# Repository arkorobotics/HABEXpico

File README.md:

# HABEXpico
Small High Altitude Balloon Payload

# Build & Flash Firmware
See /Firmware/README.md

# Run Test Suite
See /Testscripts/README.md

# TODO

- [DONE] Create NMEA and Nanoformat test scripts
- [DONE] Write NMEA parser library
- [DONE] Write Nanoformatter library
- [DONE] Test NMEA and Nanoformatter libraries using test script
- Write Radio lib
- Test Radio lib using test script
- Write Power Management lib
- Test Power Management lib using test scripts
- Write C&DH + state machine
- Test C&DH + state machine
- Bonus: Add VOR rx/triangulation with GPS ground truth and/or fallback (going to need a lot more memory)

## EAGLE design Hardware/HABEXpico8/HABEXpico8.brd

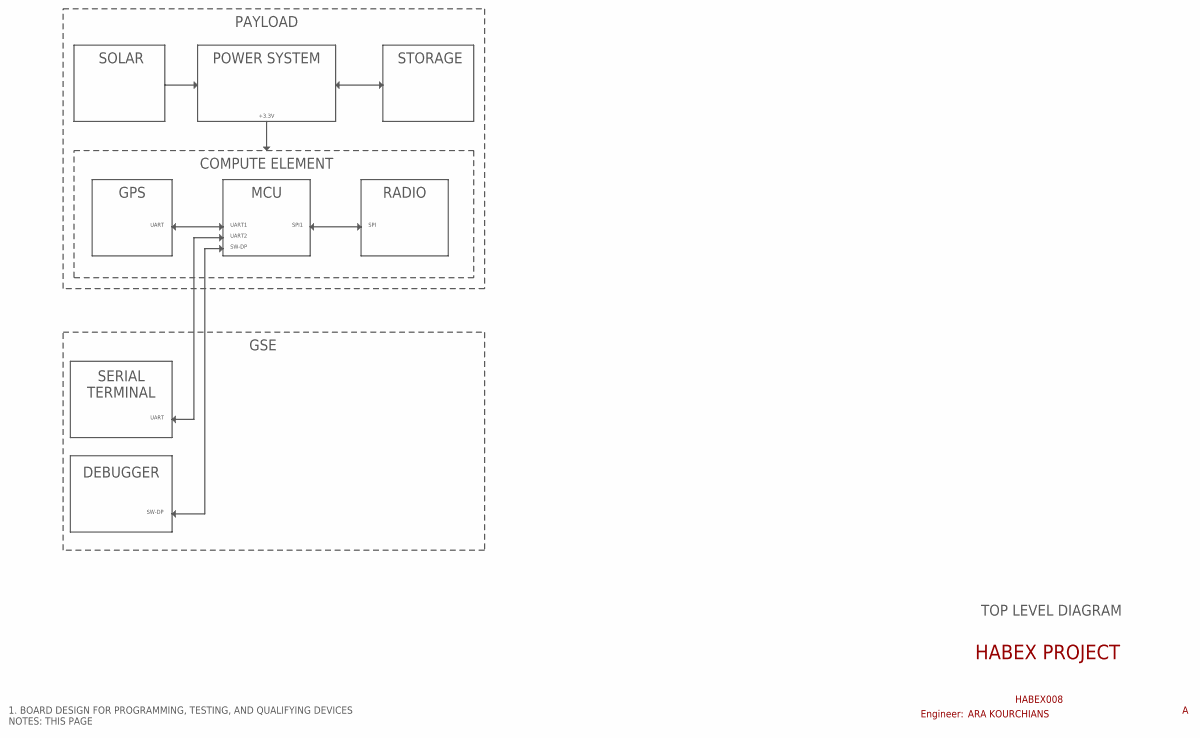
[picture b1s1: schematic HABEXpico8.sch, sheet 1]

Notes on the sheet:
1. BOARD DESIGN FOR PROGRAMMING, TESTING, AND QUALIFYING DEVICES NOTES: THIS PAGE
HABEX PROJECT
HABEX008
RADIO
MCU
GPS
UART
UART1
SPI1
SPI
ARA KOURCHIANS
Engineer:
TOP LEVEL DIAGRAM
SERIAL TERMINAL
COMPUTE ELEMENT
POWER SYSTEM
+3.3V
SOLAR
STORAGE
UART2
PAYLOAD
DEBUGGER
SW-DP
GSE

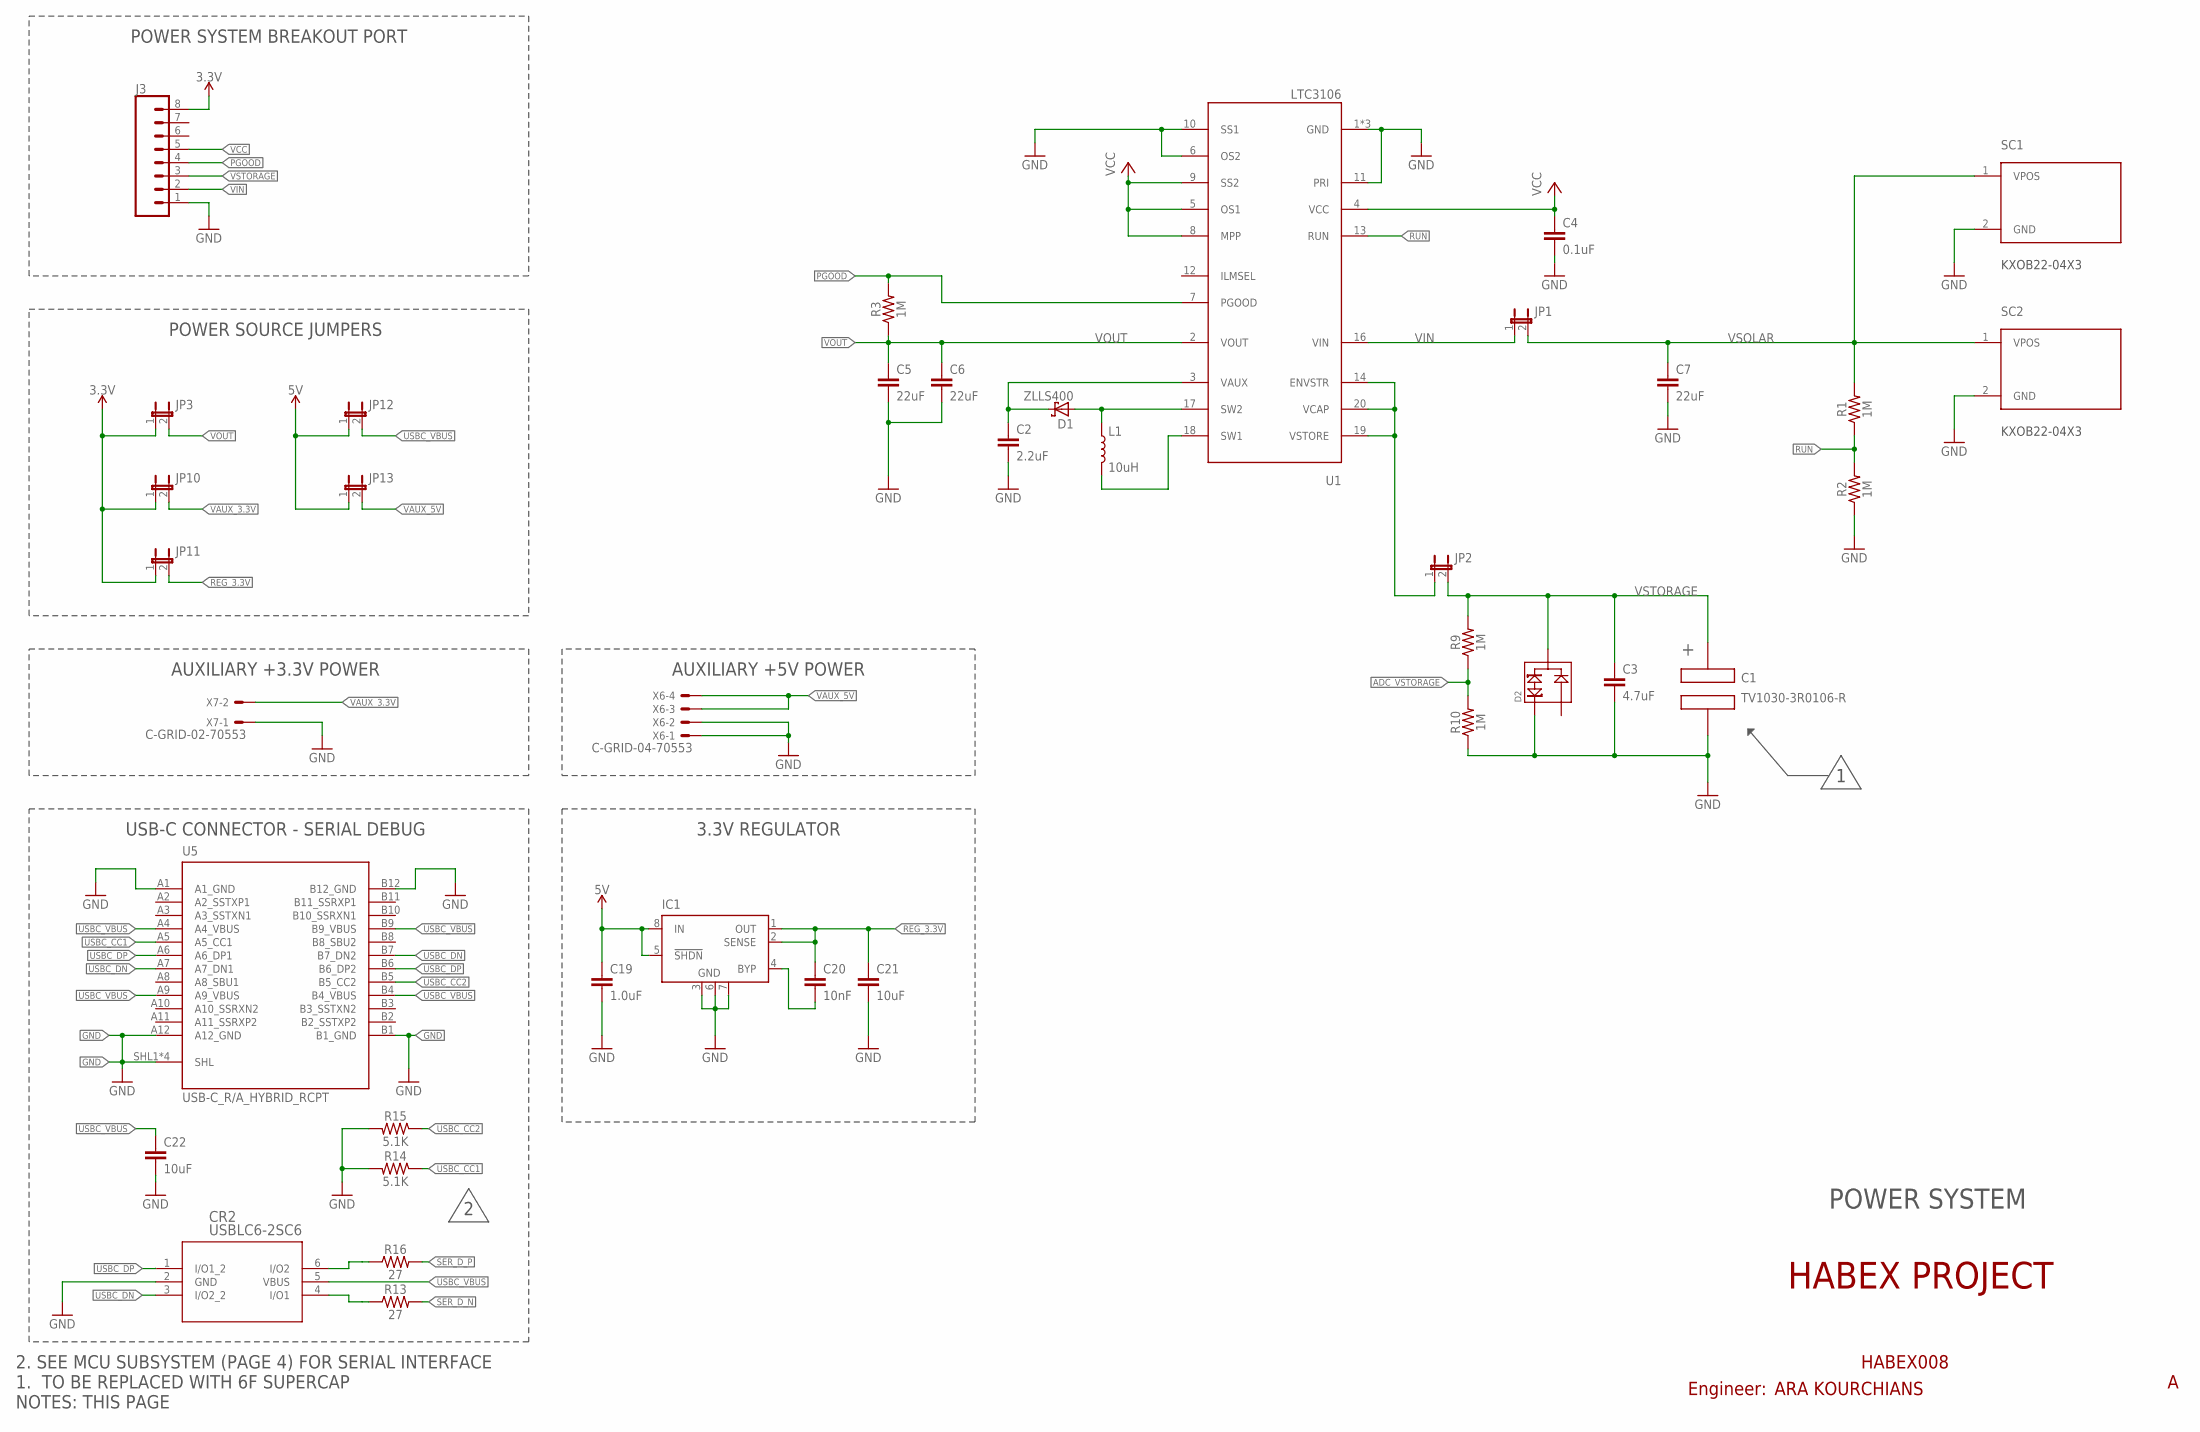
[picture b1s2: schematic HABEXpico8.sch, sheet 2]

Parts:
C1: TV1030-3R0106-R; 5.0MM-SUPERCAP
C2: 2.2uF; 0603
C3: 4.7uF; 0603
C4: 0.1uF; 0603
C5, C6, C7: 22uF; 0805
C19: 1.0uF; 0603
C20: 10nF; 0603
C21: 10uF; 0603
C22: 10uF; 0805
CR2: USBLC6-2SC6; SOT23-6L
D1: ZLLS400; SOD-323
D2: SLVU2.8HTG; SOT-23
IC1: LT1763CS8-3.3; SOIC8
J3: CONN_08"; 1X08
JP1, JP2, JP3, JP10, JP11, JP12, JP13: JUMPER-2PTH; 1X02
L1: 10uH; 1210-INDUCTOR
R1, R2, R3, R9, R10: 1M; 0603
R13, R16: 27; 0603
R14, R15: 5.1K; 0603
SC1, SC2: KXOB22-04X3; KX0B22
U1: LTC3106; UDC20QFN
U5: USB-C_R/A_HYBRID_RCPT
X6: C-GRID-04-70553; 70553-04
X7: C-GRID-02-70553; 70553-02

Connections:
2: D2.2
3.3V: J3.8, JP3.1, JP10.1, JP11.1; also elsewhere on the board
5V: C19.1, IC1.5 (!SHDN), IC1.8 (IN), JP12.1, JP13.1; also elsewhere on the board
ADC_VSTORAGE: R9.1, R10.2; also elsewhere on the board
GND: C1.2 (CAP_NEG), C2.2, C3.2, C4.2, C5.2, C6.2, C7.2, C19.2, C21.2, C22.2, CR2.2 (GND), D2.1, IC1.3 (GND), IC1.6 (GND), IC1.7 (GND), J3.1, R2.1, R10.1, R14.2, R15.2, SC1.2 (GND), SC2.2 (GND), U1.1 (GND), U1.6 (OS2), U1.10 (SS1), U1.11 (PRI), U1.15 (GND), U1.21 (GND), U5.A1 (A1_GND), U5.A12 (A12_GND), U5.B1 (B1_GND), U5.B12 (B12_GND), U5.SHL1 (SHL), U5.SHL2 (SHL), U5.SHL3 (SHL), U5.SHL4 (SHL), X6.1, X6.2, X7.1; also elsewhere on the board
unnamed: D1.A, L1.1, U1.17 (SW2)
unnamed: L1.2, U1.18 (SW1)
unnamed: C2.1, D1.C, U1.3 (VAUX)
unnamed: JP2.1, U1.14 (ENVSTR), U1.19 (VSTORE), U1.20 (VCAP)
unnamed: CR2.6 (I/O2), R16.1
unnamed: CR2.4 (I/O1), R13.1
unnamed: C20.2, IC1.4 (BYP)
PGOOD: J3.4, R3.2, U1.7 (PGOOD)
REG_3.3V: C20.1, C21.1, IC1.1 (OUT), IC1.2 (SENSE), JP11.2
RUN: R1.1, R2.2, U1.13 (RUN)
SER_D_N: R13.2; also elsewhere on the board
SER_D_P: R16.2; also elsewhere on the board
USBC_CC1: R14.1, U5.A5 (A5_CC1)
USBC_CC2: R15.1, U5.B5 (B5_CC2)
USBC_DN: CR2.3 (I/O2_2), U5.A7 (A7_DN1), U5.B7 (B7_DN2)
USBC_DP: CR2.1 (I/O1_2), U5.A6 (A6_DP1), U5.B6 (B6_DP2)
USBC_VBUS: C22.1, CR2.5 (VBUS), JP12.2, U5.A4 (A4_VBUS), U5.A9 (A9_VBUS), U5.B4 (B4_VBUS), U5.B9 (B9_VBUS)
VAUX_3.3V: JP10.2, X7.2
VAUX_5V: JP13.2, X6.3, X6.4
VCC: C4.1, J3.5, U1.4 (VCC), U1.5 (OS1), U1.8 (MPP), U1.9 (SS2)
VIN: J3.2, JP1.1, U1.16 (VIN)
VOUT: C5.1, C6.1, JP3.2, R3.1, U1.2 (VOUT)
VSOLAR: C7.1, JP1.2, R1.2, SC1.1 (VPOS), SC2.1 (VPOS)
VSTORAGE: C1.1 (CAP_POS), C3.1, D2.3, J3.3, JP2.2, R9.2

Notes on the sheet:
2. SEE MCU SUBSYSTEM (PAGE 4) FOR SERIAL INTERFACE 1. TO BE REPLACED WITH 6F SUPERCAP NOTES: THIS PAGE
HABEX PROJECT
HABEX008
POWER SYSTEM BREAKOUT PORT
ARA KOURCHIANS
Engineer:
POWER SYSTEM
POWER SOURCE JUMPERS
AUXILIARY +3.3V POWER
USB-C CONNECTOR - SERIAL DEBUG
3.3V REGULATOR
AUXILIARY +5V POWER

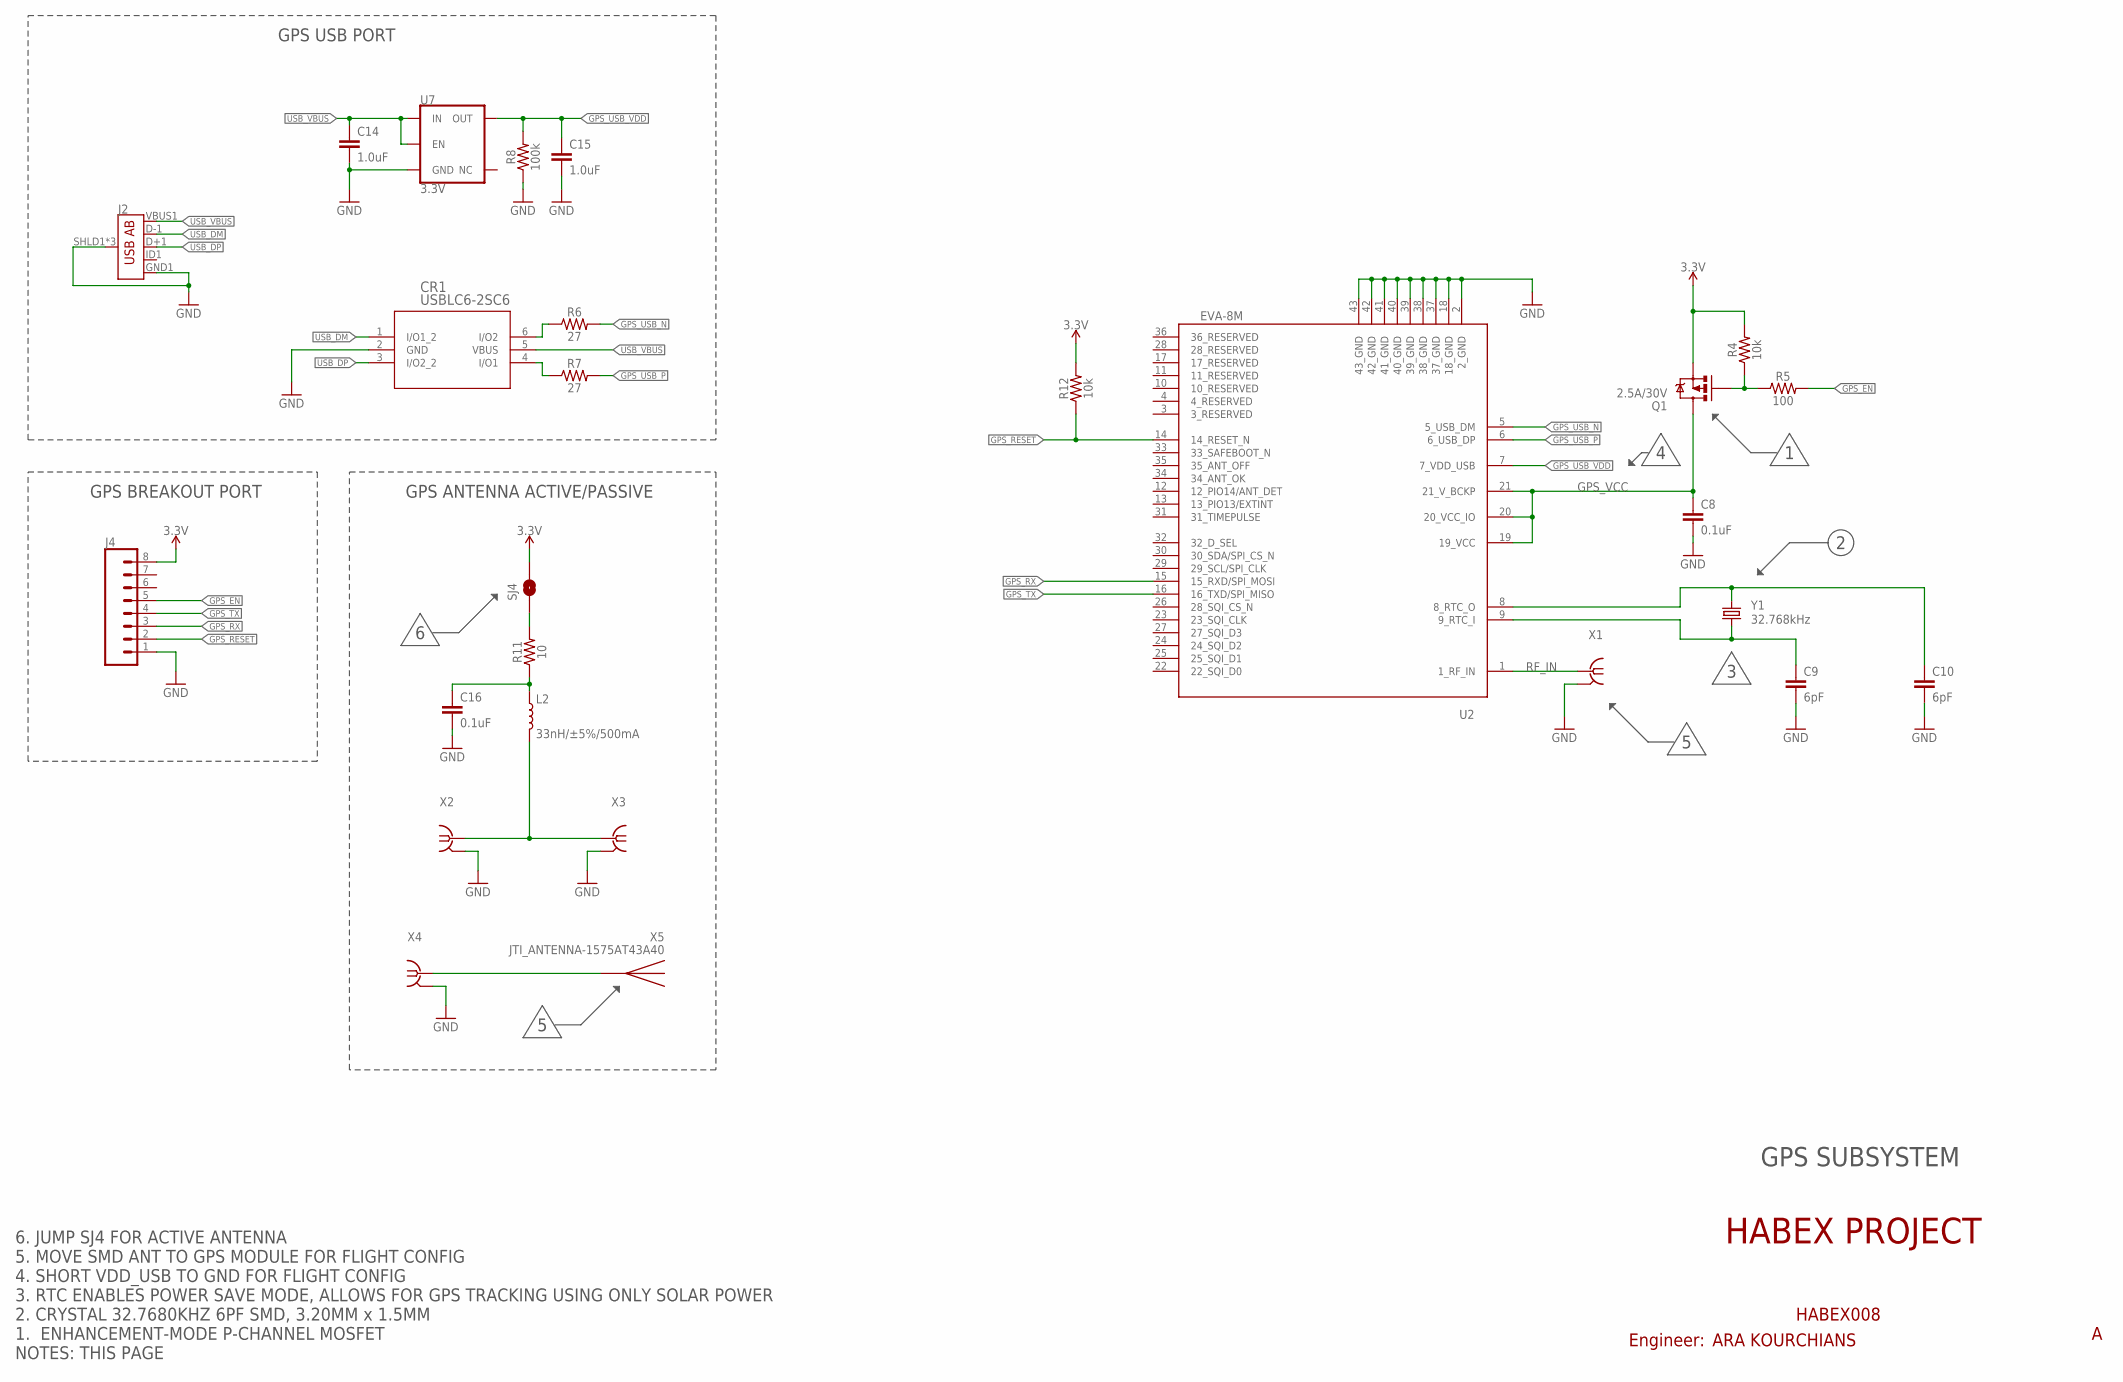
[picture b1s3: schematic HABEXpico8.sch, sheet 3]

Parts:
C8, C16: 0.1uF; 0603
C9, C10: 6pF; C0603
C14, C15: 1.0uF; 0603
CR1: USBLC6-2SC6; SOT23-6L
J2: USB_AB_SMT; USB-AB-MICRO-SMD
J4: CONN_08"; 1X08
L2: 33nH/±5%/500mA; 0603
Q1: 2.5A/30V; SOT23-3
R4, R12: 10k; 0603
R5: 100; 0603
R6, R7: 27; 0603
R8: 100k; 0603
R11: 10; 1206
SJ4: SOLDERJUMPERNO; SJ_2S-NO
U2: EVA-8M
U7: 3.3V; SOT23-5
X1, X2, X3, X4: BU-SMA-V
X5: JTI_ANTENNA-1575AT43A40
Y1: 32.768kHz; CRYSTAL-SMD-3.2X1.5MM

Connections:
3.3V: J4.8, Q1.2 (S), R4.2, R12.2, SJ4.2; also elsewhere on the board
GND: C8.2, C9.2, C10.2, C14.2, C15.2, C16.2, CR1.2 (GND), J2.GND1 (GND), J2.SHLD1 (SHIELD), J2.SHLD2 (SHIELD), J2.SHLD3 (SHIELD), J4.1, R8.1, U2.2 (2_GND), U2.18 (18_GND), U2.37 (37_GND), U2.38 (38_GND), U2.39 (39_GND), U2.40 (40_GND), U2.41 (41_GND), U2.42 (42_GND), U2.43 (43_GND), U7.2 (GND), X1.2, X1.3 (2), X1.4 (2), X1.5 (2), X2.2, X2.3 (2), X2.4 (2), X2.5 (2), X3.2, X3.3 (2), X3.4 (2), X3.5 (2), X4.2, X4.3 (2), X4.4 (2), X4.5 (2); also elsewhere on the board
GPS_EN: J4.5, R5.2; also elsewhere on the board
GPS_RESET: J4.2, R12.1, U2.14 (14_RESET_N)
GPS_RX: J4.3, U2.15 (15_RXD/SPI_MOSI); also elsewhere on the board
GPS_TX: J4.4, U2.16 (16_TXD/SPI_MISO); also elsewhere on the board
GPS_USB_N: R6.2, U2.5 (5_USB_DM)
GPS_USB_P: R7.2, U2.6 (6_USB_DP)
GPS_USB_VDD: C15.1, R8.2, U2.7 (7_VDD_USB), U7.5 (OUT)
GPS_VCC: C8.1, Q1.3 (D), U2.19 (19_VCC), U2.20 (20_VCC_IO), U2.21 (21_V_BCKP)
unnamed: X4.1, X5.FEED
unnamed: Q1.1 (G), R4.1, R5.1
unnamed: C9.1, U2.9 (9_RTC_I), Y1.P$1 (1)
unnamed: C10.1, U2.8 (8_RTC_O), Y1.P$2 (2)
unnamed: CR1.6 (I/O2), R6.1
unnamed: CR1.4 (I/O1), R7.1
unnamed: C16.1, L2.1, R11.1
unnamed: L2.2, X2.1, X3.1
unnamed: R11.2, SJ4.1
RF_IN: U2.1 (1_RF_IN), X1.1
USB_DM: CR1.1 (I/O1_2), J2.D-1 (D-)
USB_DP: CR1.3 (I/O2_2), J2.D+1 (D+)
USB_VBUS: C14.1, CR1.5 (VBUS), J2.VBUS1 (VBUS), U7.1 (IN), U7.3 (EN)

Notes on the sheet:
6. JUMP SJ4 FOR ACTIVE ANTENNA 5. MOVE SMD ANT TO GPS MODULE FOR FLIGHT CONFIG 4. SHORT VDD_USB TO GND FOR FLIGHT CONFIG 3. RTC ENABLES POWER SAVE MODE, ALLOWS FOR GPS TRACKING USING ONLY SOLAR POWER 2. CRYSTAL 32.7680KHZ 6PF SMD, 3.20MM x 1.5MM 1. ENHANCEMENT-MODE P-CHANNEL MOSFET NOTES: THIS PAGE
HABEX PROJECT
HABEX008
GPS USB PORT
ARA KOURCHIANS
Engineer:
GPS BREAKOUT PORT
GPS ANTENNA ACTIVE/PASSIVE
GPS SUBSYSTEM

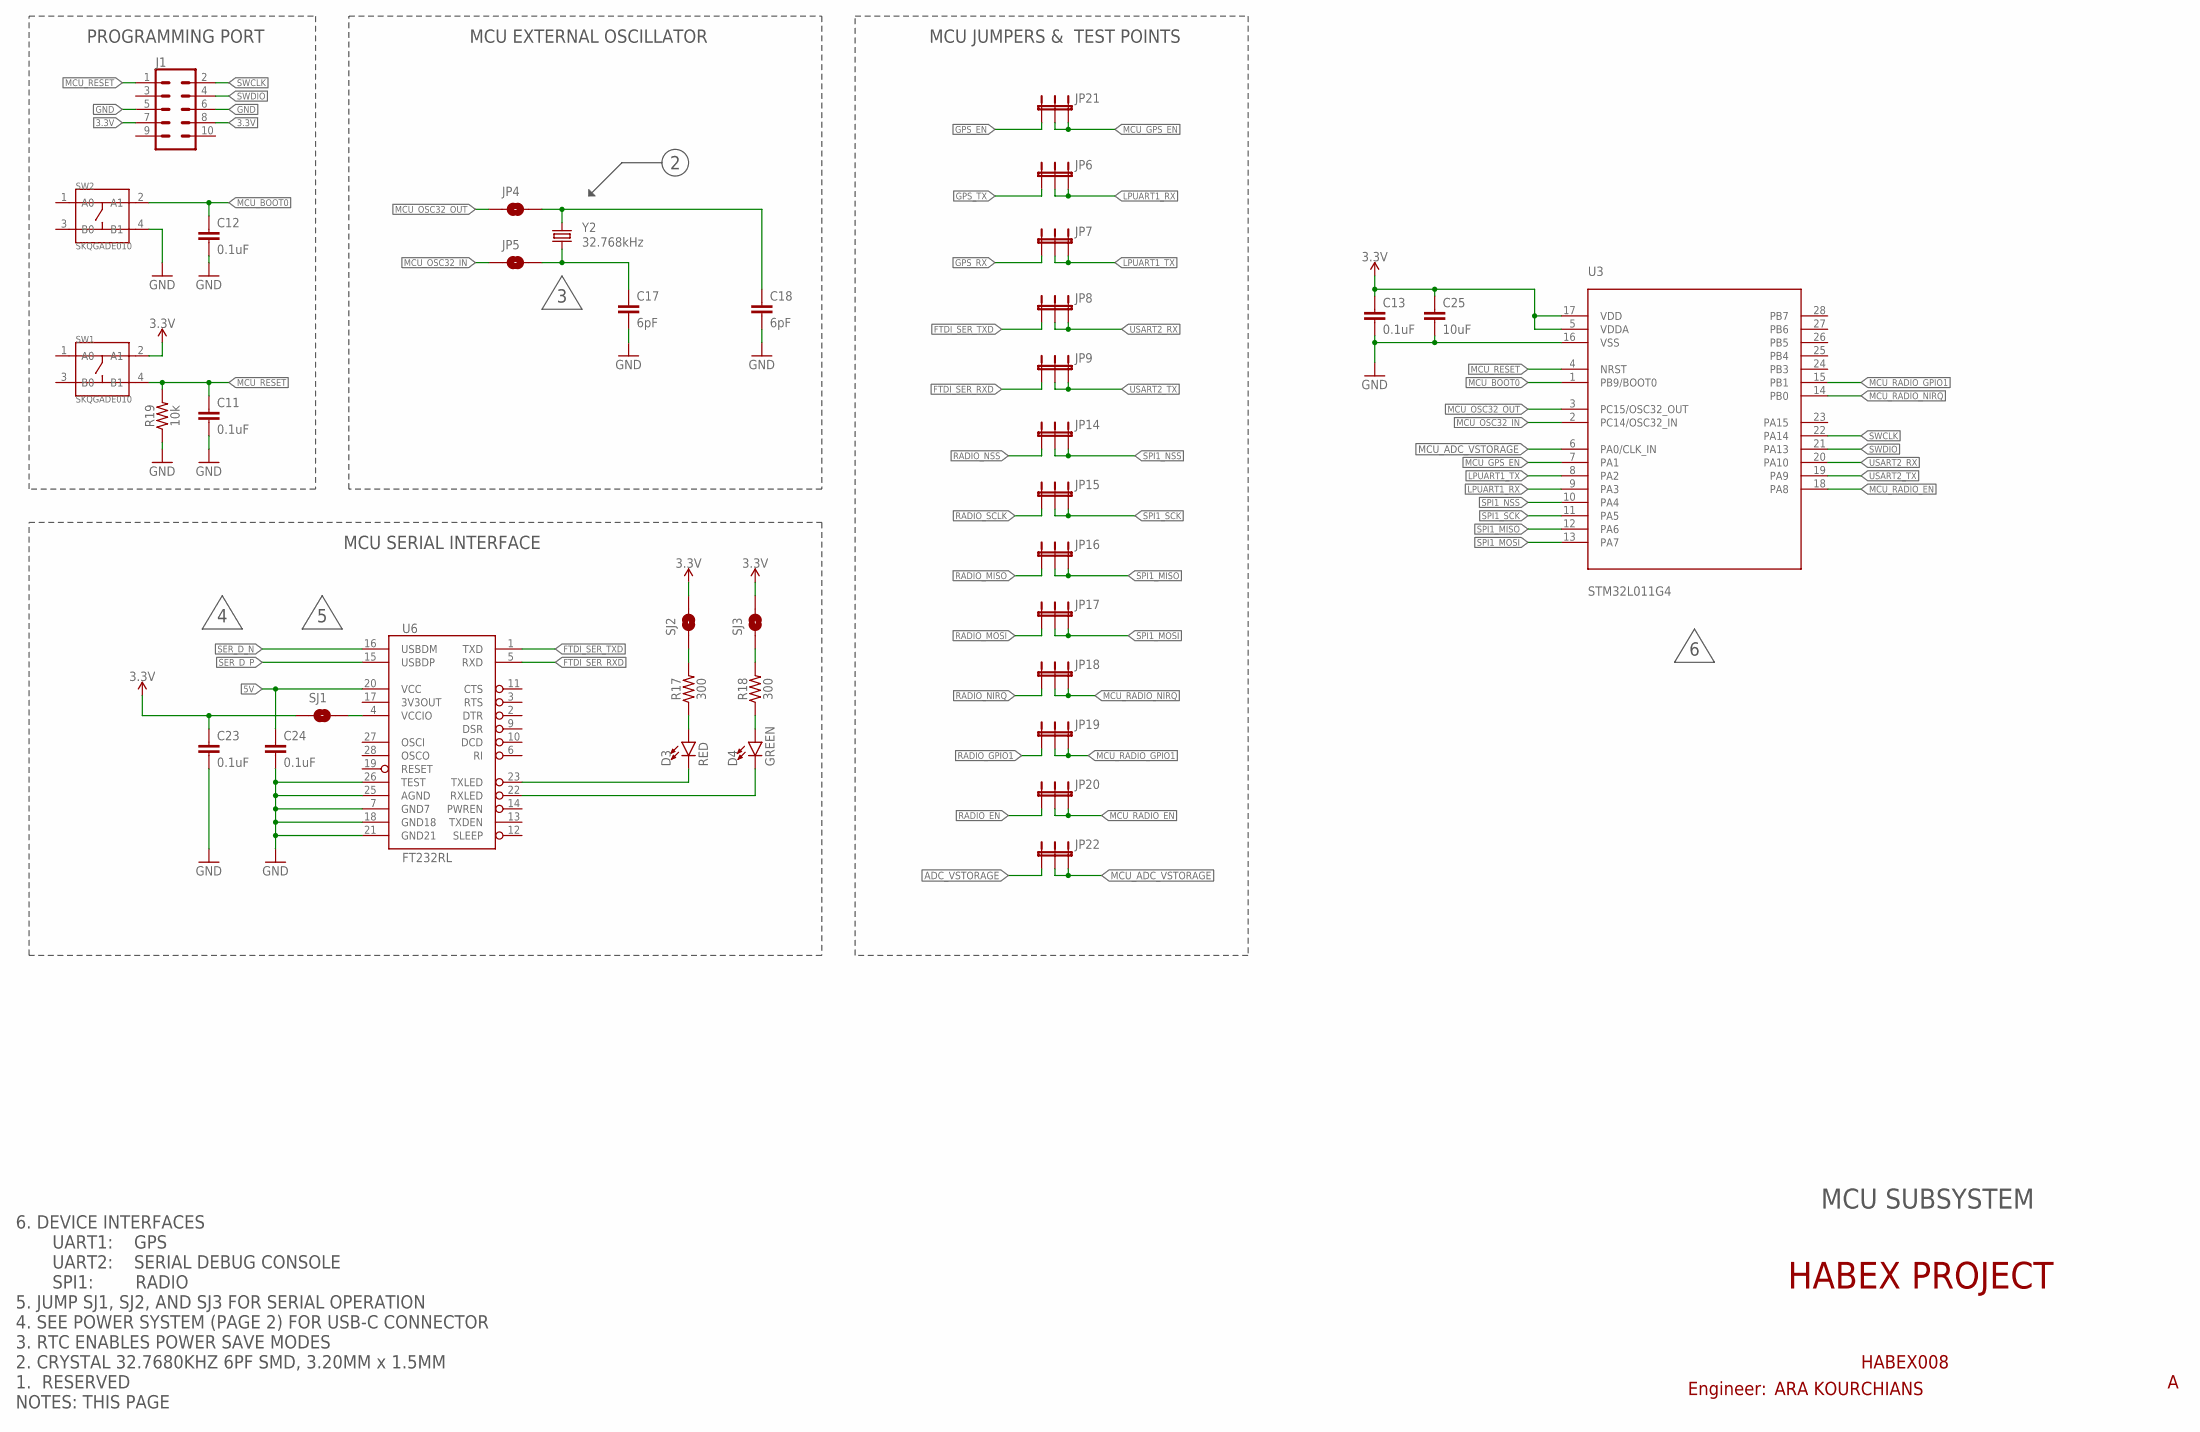
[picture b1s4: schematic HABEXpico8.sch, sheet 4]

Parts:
C11, C12, C13, C23, C24: 0.1uF; 0603
C17, C18: 6pF; C0603
C25: 10uF; 0603
D3: RED; LED-0603
D4: GREEN; LED-0603
J1: CONN_05X2SHD; 2X5-SHROUDED
JP4, JP5: JUMPER-SMT_2_NO_SILK; SMT-JUMPER_2_NO_SILK
JP6, JP7, JP8, JP9, JP14, JP15, JP16, JP17, JP18, JP19, JP20, JP21, JP22: JUMPER-3PTH; 1X03
R17, R18: 300; 0603
R19: 10k; 0603
SJ1, SJ2, SJ3: SOLDERJUMPERNO; SJ_2S-NO
SW1, SW2: SKQGADE010; SW4-SMD-5.2X5.2X1.5MM
U3: STM32L011G4; UFQFPN28
U6: FT232RL; SSOP28DB
Y2: 32.768kHz; CRYSTAL-SMD-3.2X1.5MM

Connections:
3.3V: C13.1, C23.1, C25.1, J1.7, J1.8, SJ1.1, SJ2.2, SJ3.2, SW1.2 (A1), U3.5 (VDDA), U3.17 (VDD); also elsewhere on the board
5V: C24.1, U6.20 (VCC); also elsewhere on the board
ADC_VSTORAGE: JP22.1; also elsewhere on the board
FTDI_SER_RXD: JP9.1, U6.5 (RXD)
FTDI_SER_TXD: JP8.1, U6.1 (TXD)
GND: C11.2, C12.2, C13.2, C17.2, C18.2, C23.2, C24.2, C25.2, J1.5, J1.6, R19.1, SW2.4 (B1), U3.16 (VSS), U6.7 (GND7), U6.18 (GND18), U6.21 (GND21), U6.25 (AGND), U6.26 (TEST); also elsewhere on the board
GPS_EN: JP21.1; also elsewhere on the board
GPS_RX: JP7.1; also elsewhere on the board
GPS_TX: JP6.1; also elsewhere on the board
LPUART1_RX: JP6.2, JP6.3, U3.9 (PA3)
LPUART1_TX: JP7.2, JP7.3, U3.8 (PA2)
MCU_ADC_VSTORAGE: JP22.2, JP22.3, U3.6 (PA0/CLK_IN)
MCU_BOOT0: C12.1, SW2.2 (A1), U3.1 (PB9/BOOT0)
MCU_GPS_EN: JP21.2, JP21.3, U3.7 (PA1)
MCU_OSC32_IN: JP5.1, U3.2 (PC14/OSC32_IN)
MCU_OSC32_OUT: JP4.1, U3.3 (PC15/OSC32_OUT)
MCU_RADIO_EN: JP20.2, JP20.3, U3.18 (PA8)
MCU_RADIO_GPIO1: JP19.2, JP19.3, U3.15 (PB1)
MCU_RADIO_NIRQ: JP18.2, JP18.3, U3.14 (PB0)
MCU_RESET: C11.1, J1.1, R19.2, SW1.4 (B1), U3.4 (NRST)
unnamed: C17.1, JP5.2, Y2.P$1 (1)
unnamed: C18.1, JP4.2, Y2.P$2 (2)
unnamed: D3.C, U6.23 (TXLED)
unnamed: D4.C, U6.22 (RXLED)
unnamed: D3.A, R17.1
unnamed: D4.A, R18.1
unnamed: SJ1.2, U6.4 (VCCIO)
unnamed: R17.2, SJ2.1
unnamed: R18.2, SJ3.1
RADIO_EN: JP20.1; also elsewhere on the board
RADIO_GPIO1: JP19.1; also elsewhere on the board
RADIO_MISO: JP16.1; also elsewhere on the board
RADIO_MOSI: JP17.1; also elsewhere on the board
RADIO_NIRQ: JP18.1; also elsewhere on the board
RADIO_NSS: JP14.1; also elsewhere on the board
RADIO_SCLK: JP15.1; also elsewhere on the board
SER_D_N: U6.16 (USBDM); also elsewhere on the board
SER_D_P: U6.15 (USBDP); also elsewhere on the board
SPI1_MISO: JP16.2, JP16.3, U3.12 (PA6)
SPI1_MOSI: JP17.2, JP17.3, U3.13 (PA7)
SPI1_NSS: JP14.2, JP14.3, U3.10 (PA4)
SPI1_SCK: JP15.2, JP15.3, U3.11 (PA5)
SWCLK: J1.2, U3.22 (PA14)
SWDIO: J1.4, U3.21 (PA13)
USART2_RX: JP8.2, JP8.3, U3.20 (PA10)
USART2_TX: JP9.2, JP9.3, U3.19 (PA9)

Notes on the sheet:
PROGRAMMING PORT
HABEX PROJECT
HABEX008
ARA KOURCHIANS
Engineer:
6. DEVICE INTERFACES UART1: GPS UART2: SERIAL DEBUG CONSOLE SPI1: RADIO 5. JUMP SJ1, SJ2, AND SJ3 FOR SERIAL OPERATION 4. SEE POWER SYSTEM (PAGE 2) FOR USB-C CONNECTOR 3. RTC ENABLES POWER SAVE MODES 2. CRYSTAL 32.7680KHZ 6PF SMD, 3.20MM x 1.5MM 1. RESERVED NOTES: THIS PAGE
MCU SUBSYSTEM
MCU SERIAL INTERFACE
MCU EXTERNAL OSCILLATOR
MCU JUMPERS & TEST POINTS

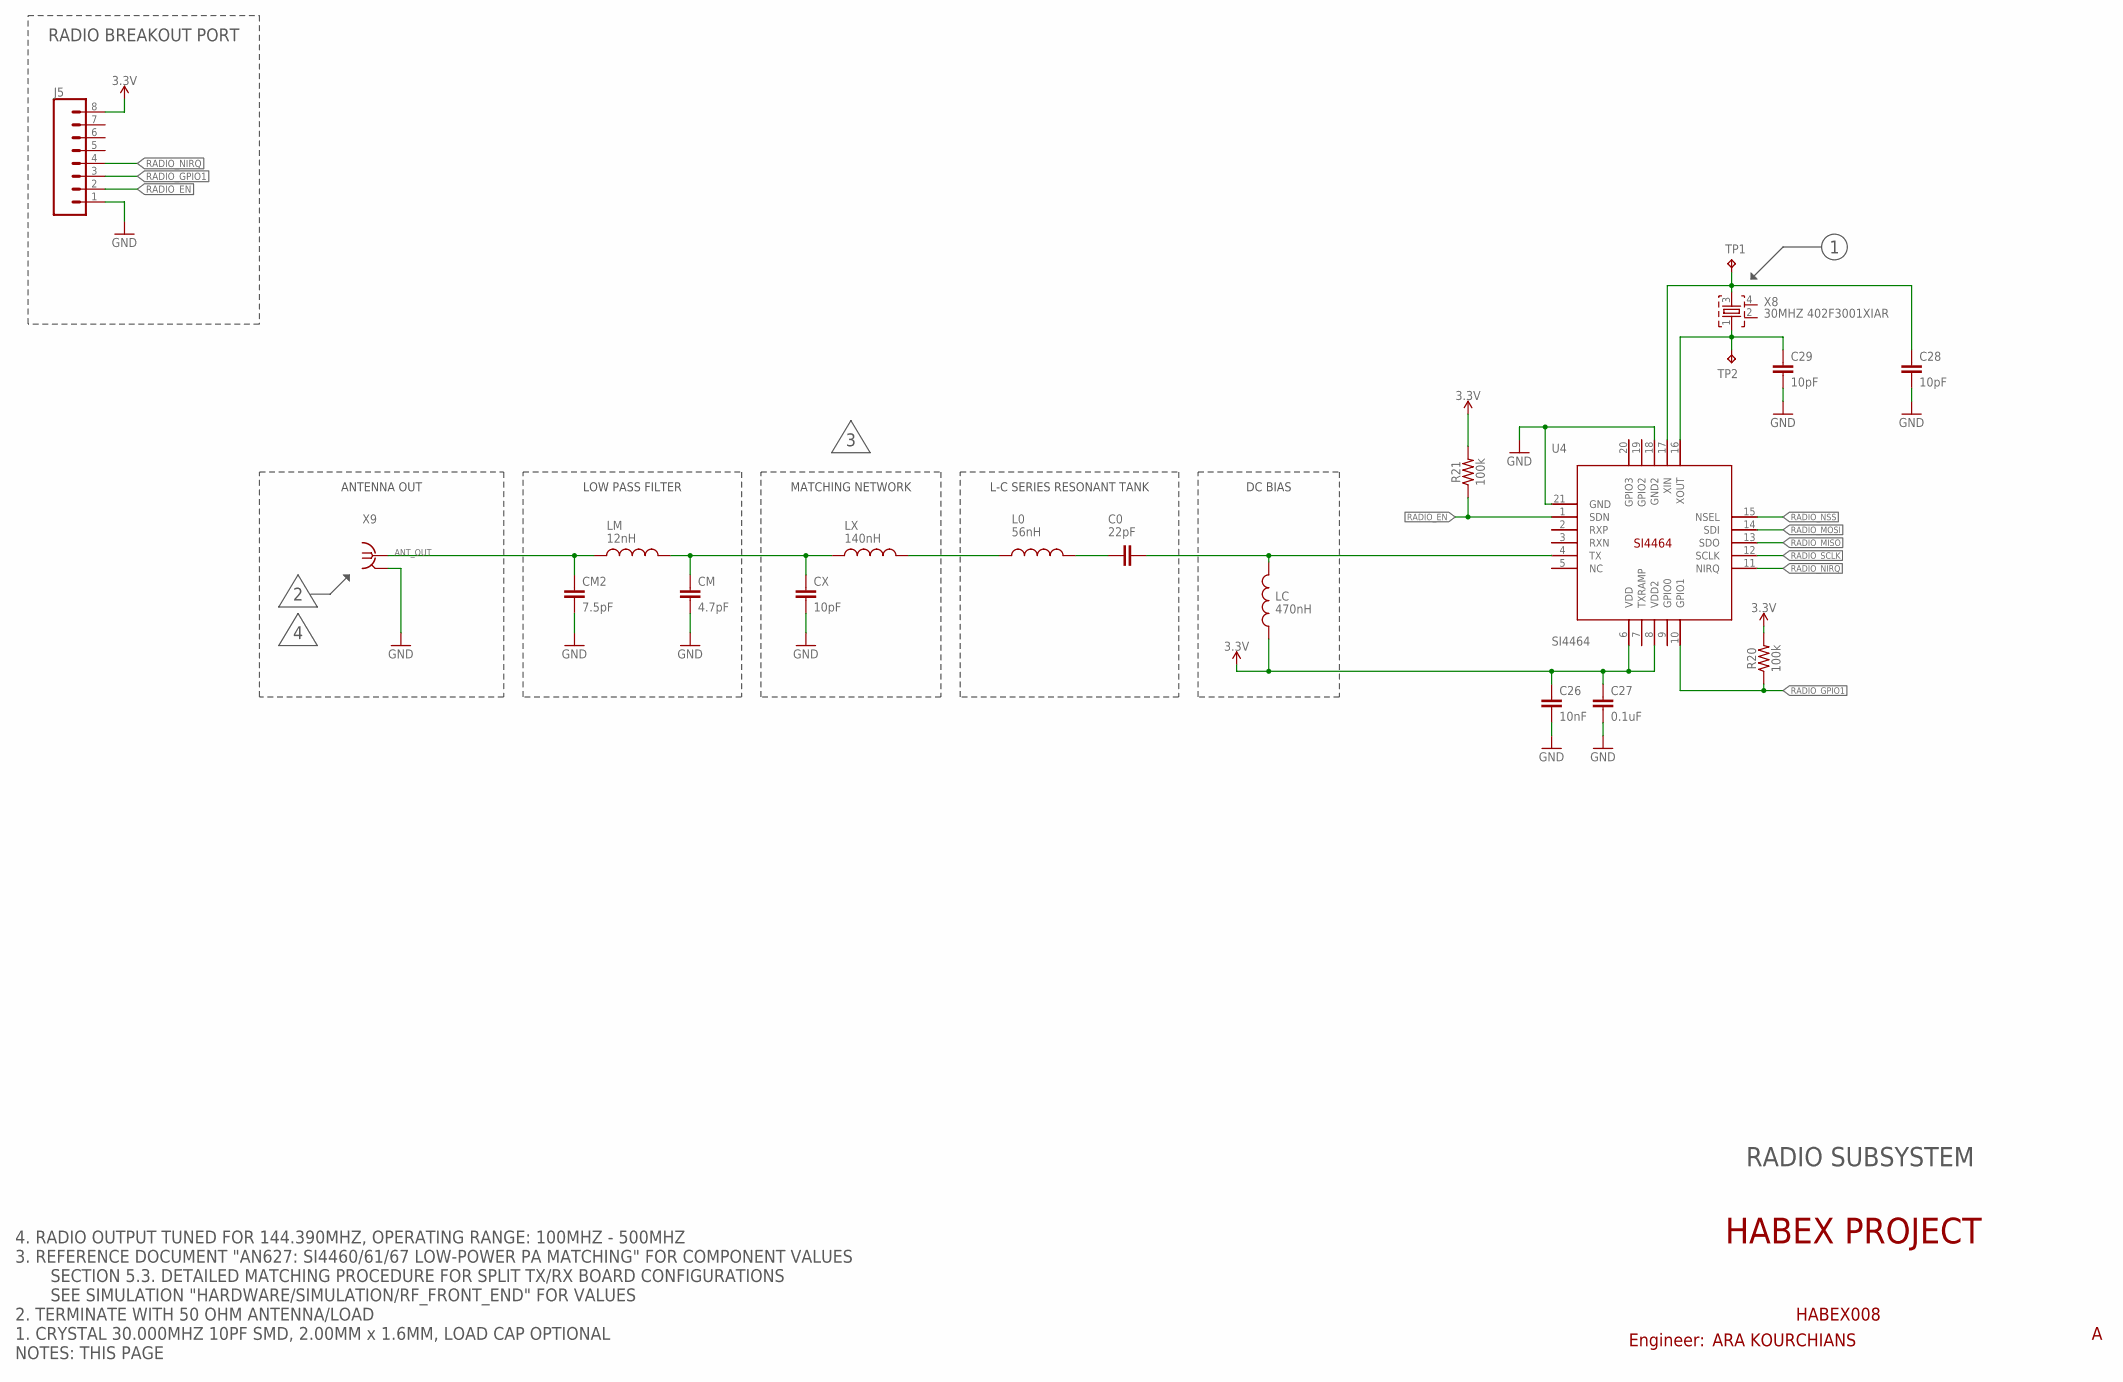
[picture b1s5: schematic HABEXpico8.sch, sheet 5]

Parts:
C0: 22pF; RESC0603_L
C26: 10nF; 0603
C27: 0.1uF; 0603
C28, C29: 10pF; 0603
CM: 4.7pF; RESC0603_L
CM2: 7.5pF; RESC0603_L
CX: 10pF; RESC0603_L
J5: CONN_08"; 1X08
L0: 56nH; RESC0603_L
LC: 470nH; RESC0603_L
LM: 12nH; RESC0603_L
LX: 140nH; RESC0603_L
R20, R21: 100k; 0603
TP1, TP2: TPPAD1-13; P1-13
U4: SI4464; QFN20+GNDPAD
X8: 30MHZ 402F3001XIAR; 2.0X1.6-4-PAD
X9: BU-SMA-V

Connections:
3.3V: C26.1, C27.1, J5.8, LC.1, R20.2, R21.2, U4.6 (VDD), U4.8 (VDD2); also elsewhere on the board
ANT_OUT: CM2.1, LM.1, X9.1
GND: C26.2, C27.2, C28.2, C29.2, CM.2, CM2.2, CX.2, J5.1, U4.18 (GND2), U4.21 (GND), X9.2, X9.3 (2), X9.4 (2), X9.5 (2); also elsewhere on the board
unnamed: C28.1, TP1.TP, U4.17 (XIN), X8.3
unnamed: C29.1, TP2.TP, U4.16 (XOUT), X8.1
unnamed: C0.1, LC.2, U4.4 (TX)
unnamed: L0.1, LX.2
unnamed: C0.2, L0.2
unnamed: CM.1, CX.1, LM.2, LX.1
RADIO_EN: J5.2, R21.1, U4.1 (SDN); also elsewhere on the board
RADIO_GPIO1: J5.3, R20.1, U4.10 (GPIO1); also elsewhere on the board
RADIO_MISO: U4.13 (SDO); also elsewhere on the board
RADIO_MOSI: U4.14 (SDI); also elsewhere on the board
RADIO_NIRQ: J5.4, U4.11 (NIRQ); also elsewhere on the board
RADIO_NSS: U4.15 (NSEL); also elsewhere on the board
RADIO_SCLK: U4.12 (SCLK); also elsewhere on the board

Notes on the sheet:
HABEX PROJECT
HABEX008
ARA KOURCHIANS
Engineer:
RADIO SUBSYSTEM
4. RADIO OUTPUT TUNED FOR 144.390MHZ, OPERATING RANGE: 100MHZ - 500MHZ 3. REFERENCE DOCUMENT "AN627: SI4460/61/67 LOW-POWER PA MATCHING" FOR COMPONENT VALUES SECTION 5.3. DETAILED MATCHING PROCEDURE FOR SPLIT TX/RX BOARD CONFIGURATIONS SEE SIMULATION "HARDWARE/SIMULATION/RF_FRONT_END" FOR VALUES 2.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
MATCHING NETWORK
LOW PASS FILTER
L-C SERIES RESONANT TANK
DC BIAS
ANTENNA OUT
RADIO BREAKOUT PORT

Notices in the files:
parts and their libraries:
SparkFun-Capacitors: Licensing: Creative Commons ShareAlike 4.0 International - https://creativecommons.org/licenses/by-sa/4.0
SparkFun-DiscreteSemi: Licensing: CC v3.0 Share-Alike You are welcome to use this library for commercial purposes.
